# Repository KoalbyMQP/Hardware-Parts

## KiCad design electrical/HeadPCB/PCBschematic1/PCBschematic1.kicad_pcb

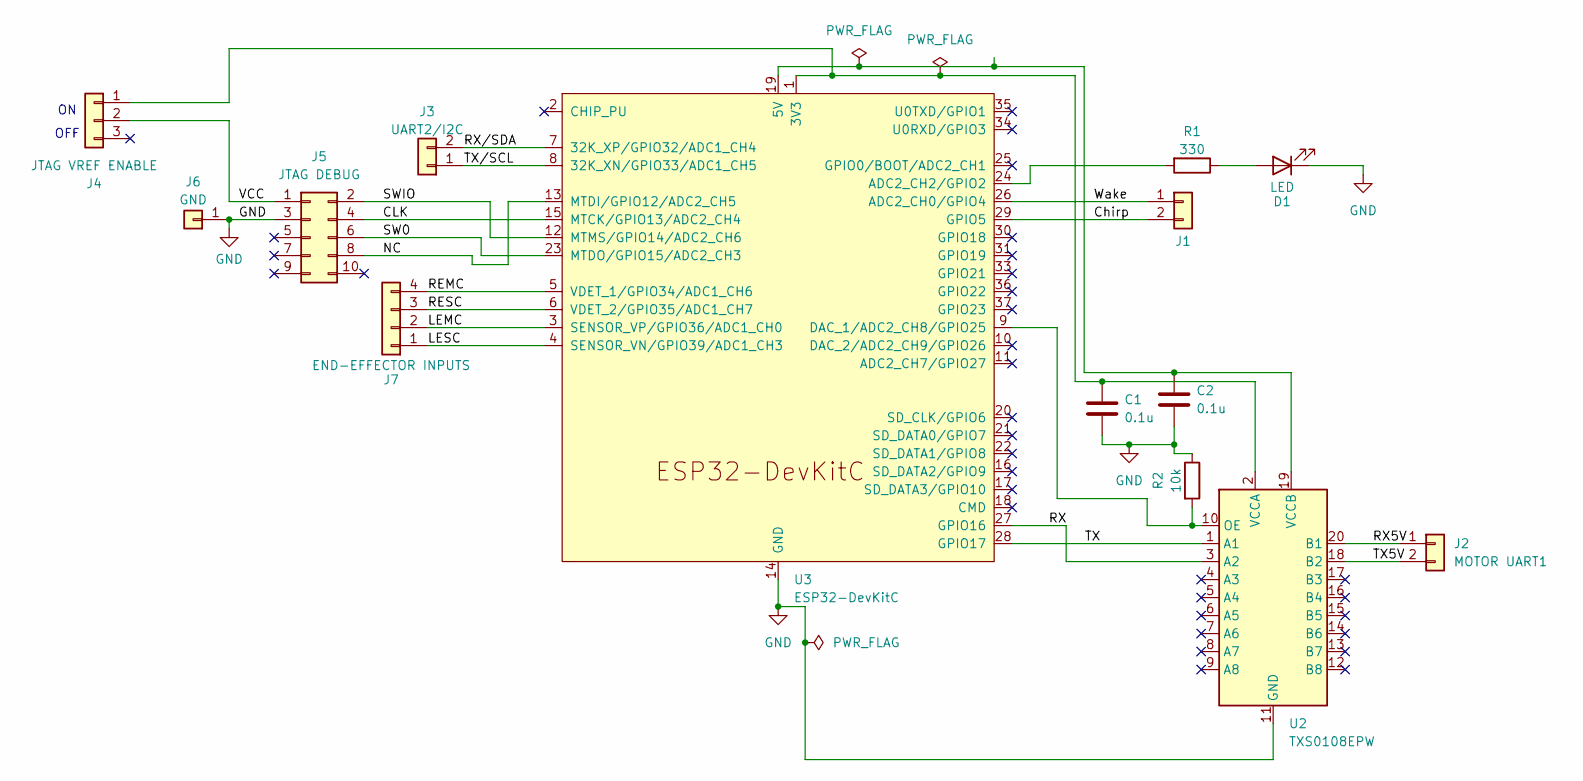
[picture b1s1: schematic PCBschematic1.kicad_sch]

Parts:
C1, C2: 0.1u; C_Axial_L3.8mm_D2.6mm_P7.50mm_Horizontal
D1: LED; LED_D5.0mm
J1: Conn_01x02; JST_XH_B2B-XH-A_1x02_P2.50mm_Vertical
J2: MOTOR UART1; JST_XH_B2B-XH-A_1x02_P2.50mm_Vertical
J3: UART2/I2C; JST_XH_B2B-XH-A_1x02_P2.50mm_Vertical
J4: JTAG VREF ENABLE; PinHeader_1x03_P2.54mm_Vertical
J5: JTAG DEBUG; PinHeader_2x05_P1.27mm_Vertical
J6: GND; PinHeader_1x01_P2.54mm_Vertical
J7: END-EFFECTOR INPUTS; JST_XH_B4B-XH-A_1x04_P2.50mm_Vertical
R1: 330; R_Axial_DIN0207_L6.3mm_D2.5mm_P7.62mm_Horizontal
R2: 10k; R_Axial_DIN0207_L6.3mm_D2.5mm_P7.62mm_Horizontal
U2: TXS0108EPW; TSSOP-20_4.4x6.5mm_P0.65mm
U3: ESP32-DevKitC

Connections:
/CLK: J5.4, U3.15 (MTCK/GPIO13/ADC2_CH4)
/Chirp: J1.2, U3.29 (GPIO5)
/LEMC: J7.2, U3.3 (SENSOR_VP/GPIO36/ADC1_CH0)
/LESC: J7.1, U3.4 (SENSOR_VN/GPIO39/ADC1_CH3)
/NC: J5.8, U3.13 (MTDI/GPIO12/ADC2_CH5)
/REMC: J7.4, U3.5 (VDET_1/GPIO34/ADC1_CH6)
/RESC: J7.3, U3.6 (VDET_2/GPIO35/ADC1_CH7)
/RX: U2.3 (A2), U3.27 (GPIO16)
/RX5V: J2.1, U2.20 (B1)
/RX/SDA: J3.2, U3.7 (32K_XP/GPIO32/ADC1_CH4)
/SW0: J5.6, U3.23 (MTDO/GPIO15/ADC2_CH3)
/SWIO: J5.2, U3.12 (MTMS/GPIO14/ADC2_CH6)
/TX: U2.1 (A1), U3.28 (GPIO17)
/TX5V: J2.2, U2.18 (B2)
/TX/SCL: J3.1, U3.8 (32K_XN/GPIO33/ADC1_CH5)
/VCC: J4.2, J5.1
/Wake: J1.1, U3.26 (ADC2_CH0/GPIO4)
GND: C1.2, C2.2, D1.1 (K), J5.3, J6.1 (Pin_1_1), R2.1, U2.11 (GND), U3.14 (GND), U3.32 (GND), U3.38 (GND)
unnamed: D1.2 (A), R1.1
unnamed: C1.1, J4.1, U2.2 (VCCA), U3.1 (3V3)
unnamed: R2.2, U2.10 (OE), U3.9 (DAC_1/ADC2_CH8/GPIO25)
unnamed: C2.1, U2.19 (VCCB), U3.19 (5V)
unnamed: R1.2, U3.24 (ADC2_CH2/GPIO2)

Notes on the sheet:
OFF

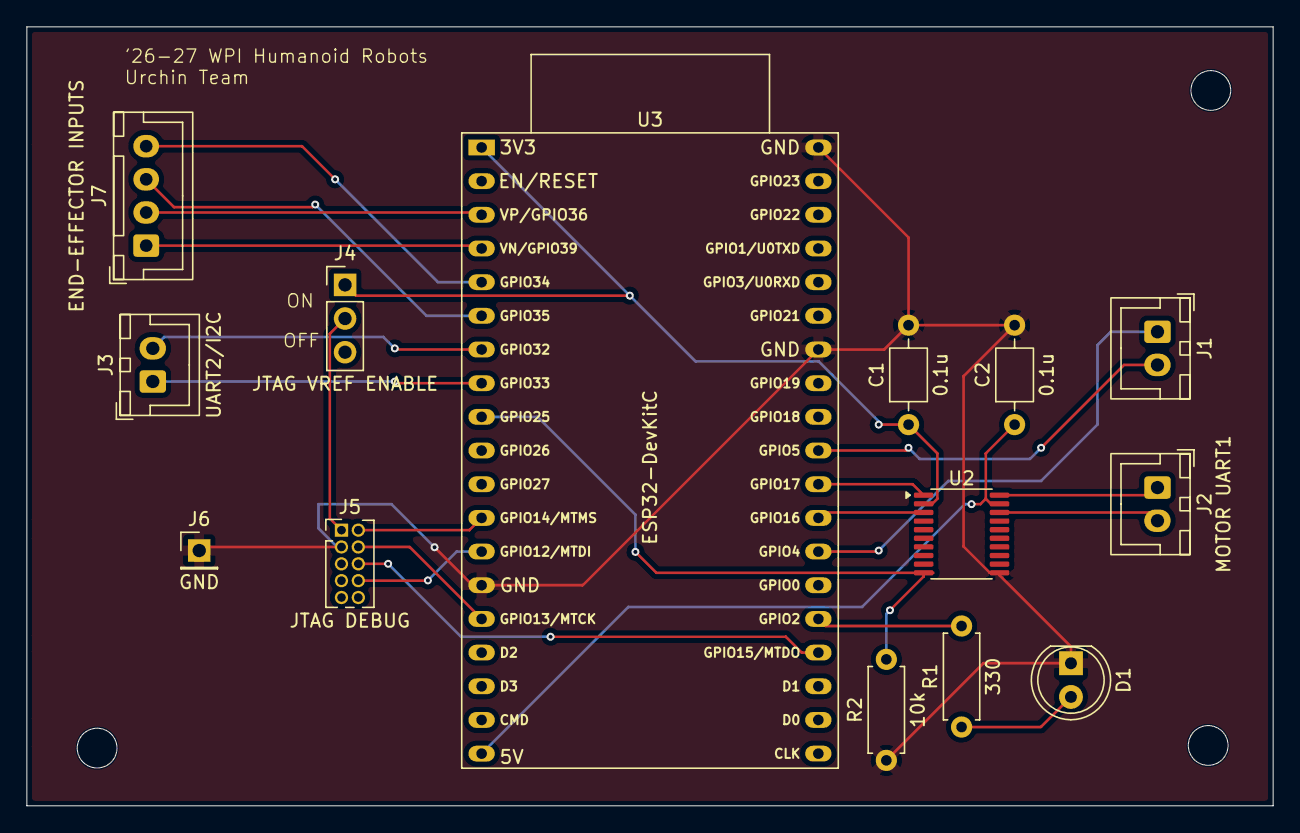
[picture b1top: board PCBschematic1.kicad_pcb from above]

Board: 2 copper layers, 94.0 x 58.8 mm, 14 parts (0 on the bottom side), 23 nets.

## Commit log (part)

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2025-07-14 Added ESP-PROG, product page and wiring diagram
2025-09-01 Uploaded updated master and sub assemblies
2025-09-01 directory update
2025-09-01 File system uprgrade and directory fixes
2025-09-03 Solidworks update
    trying to fix the foot soles
2025-09-08 Solidworks Assembly for URDF Exporting
    Uploaded the Solidworks Assembly and parts with correct link definition and naming conventions
2025-09-10 Uploaded URDF
    Exported URDF from the solidworks assembly. Currently the head is upside down and the elbows are backwards, I am working on fixing in the exporter.
2025-09-10 Updated URDF configuration
    Use Humanoid_URDF_9-10 for Nvidia IssacSim
2025-09-15 Added labels to Torso
2025-09-15 Updating Part Names pt1
2025-09-15 Deleting Master_assem pack and go folder
2025-09-18 add sample top down assembly modeling Left Leg subassm
2025-09-22 STL of New Bracket
2025-09-24 added changes to incorporate head model into CAD
2025-09-29 same as above
2025-10-03 Leg v2 to hand off to team 3
2025-10-04 moved marking to FRAME from DATA
2025-10-05 Reformated Our Ram Memory to handled Memory size ROM and RAM address Min and Max value Perm and Fucntion pointers for more detailed output
    Added S_Jog
2025-10-06 Fixed some packet errors
2025-10-06 add new pelvis assm
2025-10-06 Add temp no-horn 0601
2025-10-07 9mm Shoulder Pulley
    Made a new Shoulder and Bicep (V2) to fit a 9mm pulley. The 60t pulley will need to be 3d printed
2025-10-08 foundation for file structure, also corrected herkulex 0201
2025-10-08 cart
2025-10-08 adding gearbox files for cart
2025-10-08 hopefully not broken full assembly
2025-10-10 Transportation SystemV2
    Added the Transportation System for moving the robot around. The neck support is the only thing that does not exist right now. Created a Not in Robot folder for parts that will not be in the robot.
2025-10-16 Ran PreCommoit on Dev branch and fixed all rolint problems
2025-10-20 Dollstand(1) update
    Dollstand width reduced
2025-10-22 lots of changes
    -added end effector station from team 4
    -changed chess board assembly to include magnets for mounting
    -added a bowl for fruit storage
    -changed pill bottle sizes to be uniform
    -updated all materials on side boards to match
2025-10-22 Update side_board.SLDPRT
    Added lip to book storage
2025-10-24 Add MIT License to repository
    Resolves #32
2025-10-24 added side board with hardware
    not mounted on full assembly yet
2025-10-26 Reduced stress risers
    Reduced stress risers on arm assembly links. The V2 Bicep and the other links in the V2 part folder. Useful as a start to a V2 design if needed.
2025-10-26 updated front board with mounting hardware
2025-10-27 created book holder, started mounting hardware for gearbox
2025-10-27 re-organized files and more gearbox changes
2025-10-28 start of Bridge file
2025-10-29 fixed platform
    deleted the ballnut screw housing since it will not be used, made changes to platform, fixed mates of dollstand with elevator
2025-10-29 Doll stand version 3
    Separated the components of the doll stand, yet to include in full elevator assembly.
2025-10-30 started updating chess board assembly (not on master)
2025-10-31 completed v1 chess board lead screw assembly
2025-11-03 updated hole sizes and clearances on gearbox
2025-11-03 added Extraction on bridge file and sending to esp32
2025-11-03 Fixed init file env for unit test
2025-11-03 V2 wrist parts
2025-11-04 added holes for bolts
    added holes for the bolts for the sfu ball screw and the holes to the platform so they can attach
2025-11-04 Platform edits
    New dollstand and platform added
2025-11-04 Fixed Mate in Drivetrain and Assembly
2025-11-05 dollstand width increase
    dollstand width increase
2025-11-06 Bridge System made
2025-11-07 Thigh V2 using topology optimization
    May need to be lengthened if proportions are going to be kept. Ping me on slack if you are unable to access the files, will fix with a new commit.
2025-11-07 Version 2 of right calf
    utilized topology optimization to design the calf, to make the left the part will need to mirrored
2025-11-09 Dollstand width
    Someone check??
2025-11-10 Shoulder V2 Strengthening
2025-11-10 changed elevator lead screw length & added fastners
    still need to add fasteners for end attachments
2025-11-10 Created solid works drawing
2025-11-11 Add all the new changes, chest redesigns
2025-11-11 Add files via upload
    Calf-v2, this is 2.0.2 of the calf 0201 on the ankle got flipped around to shorten the overall length of the calf
    Thigh-v2-shell-master, this 2.0.2 offset has been adjusted and mounting solution changed slightly
2025-11-11 Rename mechanical/cad/assemblies/Redesign/leg-redesigns/topology study-Topology Study 1.CWR to mechanical/cad/assemblies/Redesign/leg-redesigns/archive/topology study-Topology Study 1.CWR
2025-11-11 Rename mechanical/cad/assemblies/Redesign/leg-redesigns/right-calf-v2.SLDPRT to mechanical/cad/assemblies/Redesign/leg-redesigns/archive/right-calf-v2.SLDPRT
2025-11-11 Rename mechanical/cad/assemblies/Redesign/leg-redesigns/topology study.SLDPRT to mechanical/cad/assemblies/Redesign/leg-redesigns/archive/topology study.SLDPRT
2025-11-11 Making the new Assembly
2025-11-12 Add foot
    Add redesigned parametric foot model
2025-11-12 Add files via upload
    suppressed McMaster hardware
2025-11-13 Found Lost EEs
    Moved the Board Game Hand and other EE files to an active branch
2025-11-13 Linear slide implement
    Added linear slide to fullcartassembly,
2025-11-14 updated gearbox input and output dimensions
2025-11-14 Added Nick's head redesign
2025-11-16 lowered chess board, resolved gearbox issues
2025-11-16 added all swapping station hardware and cad in addition to new precision end effector cad
2025-11-17 Add files via upload
    increased thickness at one part. minor change
2025-11-18 more gearbox changes
2025-11-18 Topographical Arm skeleton
2025-11-20 Update Pelvis
    Last Updates for design review updates
2025-11-21 Update foot and thigh lift
    Foot:
    - Updated screw counterbore depth
    - added PCB to foot and mounts
    Thigh Lift:
    - Strengthened part
2025-11-21 add new assemblies
2025-11-22 Updated Pelvis Parts
    Updated thigh lift in assembly to reflect current model
    Increased spacing in pelvis connector to reduce interference with chest lean connector
    Updated assembly with two configurations: 1 for zero position (locked) and 1 for a "free move" position
2025-11-24 Update motor in foot
    Updated 0201 motor file to motor from herkuleX site
2025-11-24 Sam G's knee gear box Modified
    made small modifications to Sam original design. Gearing is the same, changed mounting
2025-12-08 gt2 3mm pulley parts
    Made a printable gt2 2mm pitch pulley. Prinatable gt2 3mm pitch pulley counterparts.
2025-12-08 Final update foot
2025-12-08 Electrical tie down locations added
2025-12-09 add ava2.0 folder
2025-12-09 Updated chest
2025-12-09 updated legs
2025-12-09 Delete ava2.0 directory
    (it was a mistake)
2025-12-11 Delete ava2.0/FullAssembly_AVA_2_0.SLDASM
    about to replace with updated one with arm assembly working
2025-12-11 better arms
2025-12-11 fix arm issues with subassemblies
2025-12-11 updated all the materials for motors and links
2025-12-12 branch up to date
2025-12-12 calf update? possible assembly issues
2026-01-18 updated pelvis wire clearance
2026-01-18 Newest version of arms and wrist
    This contains the assembly files for both the arm and the wrist. We will use FEA analysis now to verify their integrity. This is good enough for visual purposes.
2026-01-19 Updated Planetary Cap
    - tolerance issue resolved
2026-01-20 Update full assm with feet sole part
2026-01-20 assembly has arms and the file structure contains up to date foot
2026-01-20 add urdf export config to assm
2026-01-20 urdf upload ava 2.0
2026-01-21 test urdf
2026-01-23 made changes to Head2.0 for board mounting and added fan holes.
2026-01-23 adjusted screen cutout, motor bracket holes, and board mounting holes, as well as head size slightly.
2026-01-26 Arm Ring Gear Edit
    - Added chamfer to teeth
    - Added M2 Countersink to mounting points
2026-01-28 Fixed interferences
    Finished sketches and assembly is fully defined. Ready for gear box
2026-01-30 finialized and polished head redesign
2026-01-30 updated head for chosen screen and started on lid
2026-02-01 Topographical study on shoulder
    Did a topographical study on the shoulder and removed material accordingly. Added hole for motor wires and other minor changes.
2026-02-02 forgot to save before last push, finished head lid v2
2026-02-02 moved head v2 assembly into this repo, need to fix subassembly and add lid
2026-02-02 Added Corner Bracket For cart
2026-02-03 created a mirrored version of new arm assemble
2026-02-03 QoL Changes
    - Added Planetary Cap
    - Added 2mm dowel pins
    - Removed M2 Screws as shafts
    - Added QoL chamfers to various parts for assembly.
2026-02-03 Created BoM .xlsx
2026-02-03 updated assembly to have no servo horn
2026-02-03 Major Arm Fixes
    - Deleted old Arms and replaced with Christians arm redesign sub-assembly
    - Imported sub-assem for easier URDF export
2026-02-03 Revert "Minor Rebuild Error Fix"
    This reverts commit 4eb1429bbb06abb4b3405e5c05e417913c946ef7.
2026-02-03 Revert "Reapply "Minor Rebuild Error Fix""
    This reverts commit 861426aeb95496a4ad825b12beb543d6cd155be4.
2026-02-03 fix references within final assembly
2026-02-03 removed arms just legs torso and head
2026-02-04 added most recent arms to left and right
2026-02-04 Added wrist assembly to master assembly
2026-02-04 fixed wrist servo reference
2026-02-04 Uploading First Draft Chess Hand
    The base piece should be converted to a configuration of the actual base used for designing the wrist
2026-02-04 references locked for motors
2026-02-04 resolved issues with legs in master assem
2026-02-05 updated drivetrain with new motors
2026-02-05 Create board
2026-02-05 Adding Chess Board Files
2026-02-05 fixed urdf mesh references for balancing/chess model
2026-02-06 updated cart with new end effector storage
2026-02-09 Added a movable arm assembly for testing
2026-02-12 Added Slot to Temp Hand
    - Added slot for dovetail
2026-02-17 Tweaked head design for new screen
2026-02-17 fixed head screen insert
2026-02-19 Bicep Wire access and shoulder tolerance
2026-02-19 edited end effector base mounting holes and nut mounting hole
2026-02-19 Additional Chess Hand Update
2026-02-26 Added Transportation Station with torso Mounting
    Added updated transportation cart with two torso mounting options for poles based on what is available.
2026-02-27 Reorganizing End Effectors folder
    Clusterfuck of a path:
    assemblies\ava2.0\Arms\Arms V3 Ava 2.0\End Effectors\
2026-02-27 New URDF export in hopes meshes are fixed
2026-02-27 Half-Done Temp and Oximeter Hand
    - Working on a more standardized temp and oximeter hand/cap
2026-03-01 Inserted Current arm parts into assembly
2026-03-03 Update to Sun Gear
    -Tolerance changes to sun gear
2026-03-05 cleanup and remake assm
    to solve usd issues
2026-03-05 URDF export
    verified with correct movements
2026-03-27 Edited Mounting Holes
    Changed the mounting holes on the motor mount from 15mm to 12.5mm from edge
2026-03-31 updates to head peices
2026-03-31 add correct screen file
2026-03-31 add head assembly
2026-03-31 Power switch in robot assembly
2026-04-02 Rail mounting attachment shifted
2026-04-09 Gripper claw re-designed for 25T servo arm
2026-04-20 Hands, Wrist, & Gearboxes
    Updated Master Assem w/ correct wrists and hands
    - New gearbox added in "gearing"
    - New wrists & hands added in "grippers"
    - These changes should ensure CAD in palcolea-torso branch is also in ava-dev
2026-04-20 Updated Master Assem
    - Ensuring Master Assem is saved w/o rebuild errors (:
2026-04-20 Added Head Lid w/ Camera
    - Created a head lid w/ camera mount location from previous head.
2026-04-20 Doll chest piece extended
2026-04-22 Added a 70x90 option for head electronic mount
2026-04-26 update to foot
    added 0601 to ankle joint
2026-04-30 add a new version of calf that includes a 0601 in the ankle. Driving assembly in the legs folder
2026-04-30 fixed final chamfers and fillets
